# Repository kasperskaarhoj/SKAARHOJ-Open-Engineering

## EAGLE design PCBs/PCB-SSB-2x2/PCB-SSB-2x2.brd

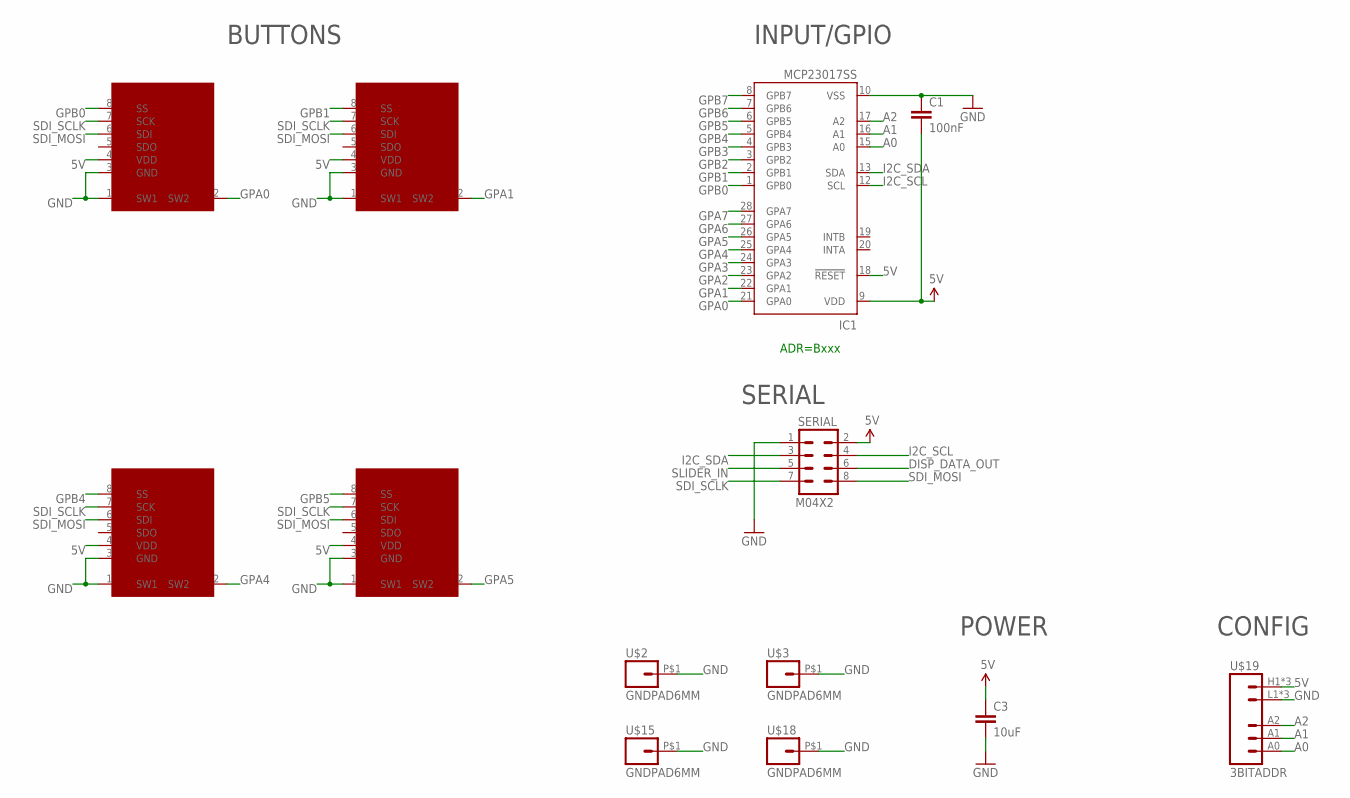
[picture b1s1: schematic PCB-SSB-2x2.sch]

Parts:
C1: 100nF; 0603-CAP
C3: 10uF; 0805
IC1: MCP23017SS; SSOP28; MPN MCP23017-E/SS
SERIAL: M04X2; 2X4
SSW1, SSW2, SSW5, SSW6: SMART_SWITCHSMART_SWITCH_8PIN; SMART_SWITCH
U$2, U$3, U$15, U$18: GNDPAD6MM; 3.2MMPAD6MM
U$19: 3BITADDR

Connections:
5V: C1.2, C3.1, IC1.9 (VDD), IC1.18 (!RESET), SERIAL.2, SSW1.4 (VDD), SSW2.4 (VDD), SSW5.4 (VDD), SSW6.4 (VDD), U$19.H1 (VCC), U$19.H2 (VCC), U$19.H3 (VCC)
A0: IC1.15 (A0), U$19.A0
A1: IC1.16 (A1), U$19.A1
A2: IC1.17 (A2), U$19.A2
DISP_DATA_OUT: SERIAL.6
GND: C1.1, C3.2, IC1.10 (VSS), SERIAL.1, SSW1.1 (SW1), SSW1.3 (GND), SSW2.1 (SW1), SSW2.3 (GND), SSW5.1 (SW1), SSW5.3 (GND), SSW6.1 (SW1), SSW6.3 (GND), U$2.P$1, U$3.P$1, U$15.P$1, U$18.P$1, U$19.L1 (GND), U$19.L2 (GND), U$19.L3 (GND)
GPA0: IC1.21 (GPA0), SSW1.2 (SW2)
GPA1: IC1.22 (GPA1), SSW2.2 (SW2)
GPA2: IC1.23 (GPA2)
GPA3: IC1.24 (GPA3)
GPA4: IC1.25 (GPA4), SSW5.2 (SW2)
GPA5: IC1.26 (GPA5), SSW6.2 (SW2)
GPA6: IC1.27 (GPA6)
GPA7: IC1.28 (GPA7)
GPB0: IC1.1 (GPB0), SSW1.8 (SS)
GPB1: IC1.2 (GPB1), SSW2.8 (SS)
GPB2: IC1.3 (GPB2)
GPB3: IC1.4 (GPB3)
GPB4: IC1.5 (GPB4), SSW5.8 (SS)
GPB5: IC1.6 (GPB5), SSW6.8 (SS)
GPB6: IC1.7 (GPB6)
GPB7: IC1.8 (GPB7)
I2C_SCL: IC1.12 (SCL), SERIAL.4
I2C_SDA: IC1.13 (SDA), SERIAL.3
SDI_MOSI: SERIAL.8, SSW1.6 (SDI), SSW2.6 (SDI), SSW5.6 (SDI), SSW6.6 (SDI)
SDI_SCLK: SERIAL.7, SSW1.7 (SCK), SSW2.7 (SCK), SSW5.7 (SCK), SSW6.7 (SCK)
SLIDER_IN: SERIAL.5

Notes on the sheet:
ADR=Bxxx
INPUT/GPIO
POWER
SERIAL
BUTTONS
CONFIG

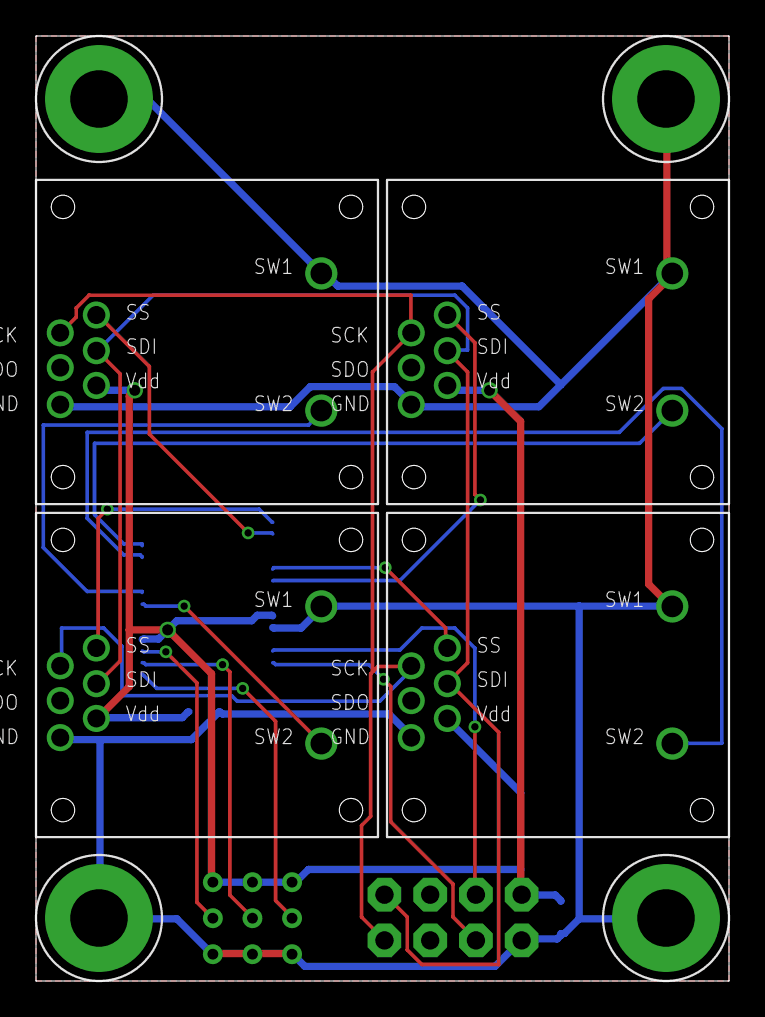
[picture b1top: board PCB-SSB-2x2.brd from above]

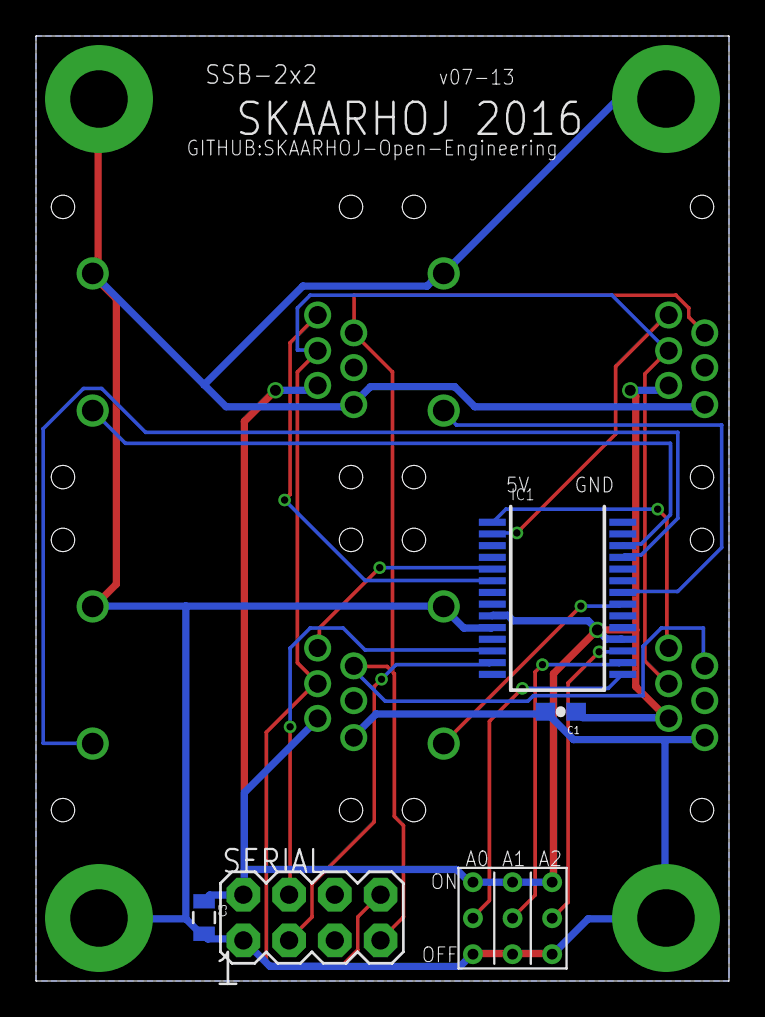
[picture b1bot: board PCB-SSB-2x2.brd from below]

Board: 2 copper layers, 38.5 x 52.5 mm, 13 parts (5 on the bottom side), 17 nets.

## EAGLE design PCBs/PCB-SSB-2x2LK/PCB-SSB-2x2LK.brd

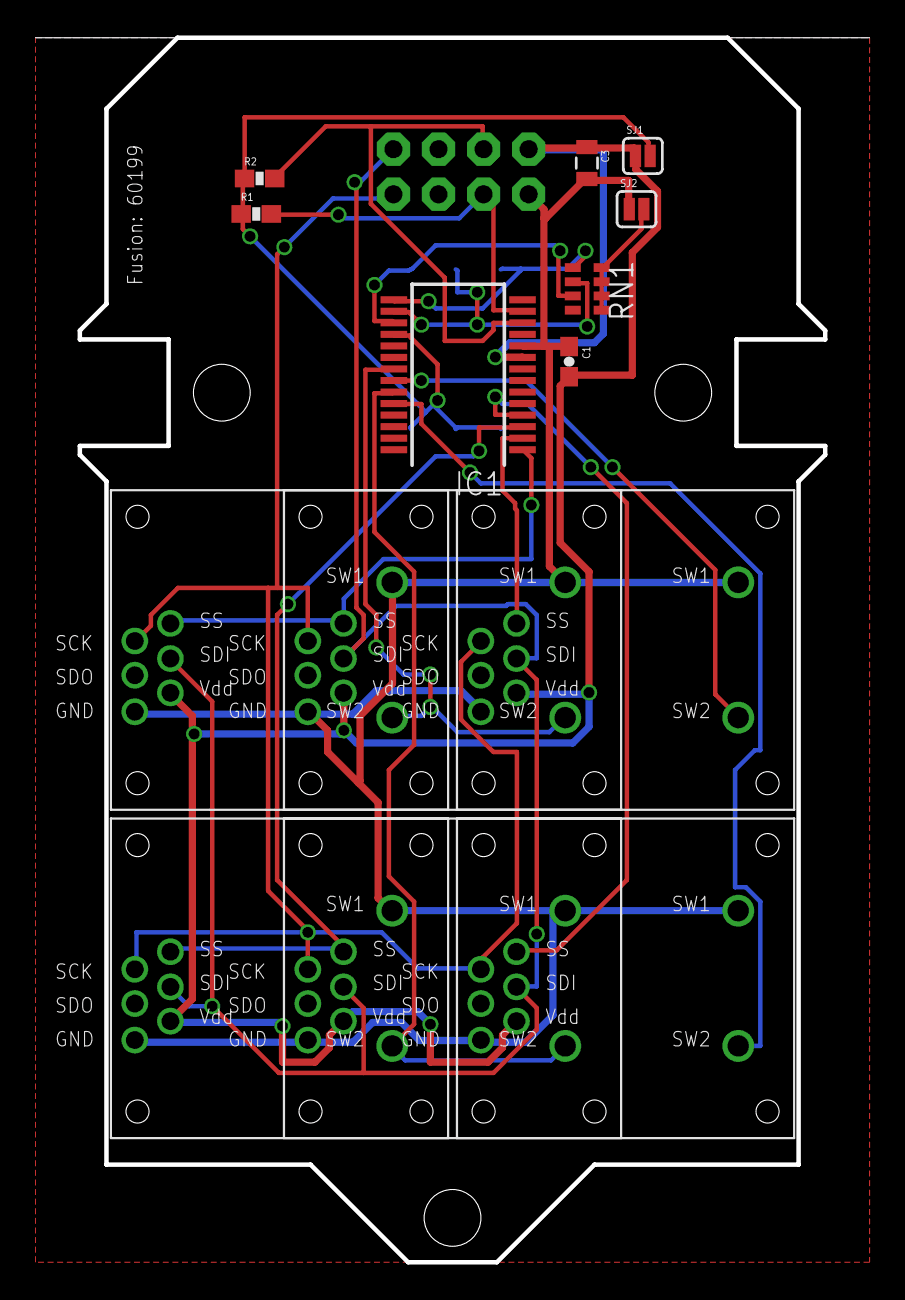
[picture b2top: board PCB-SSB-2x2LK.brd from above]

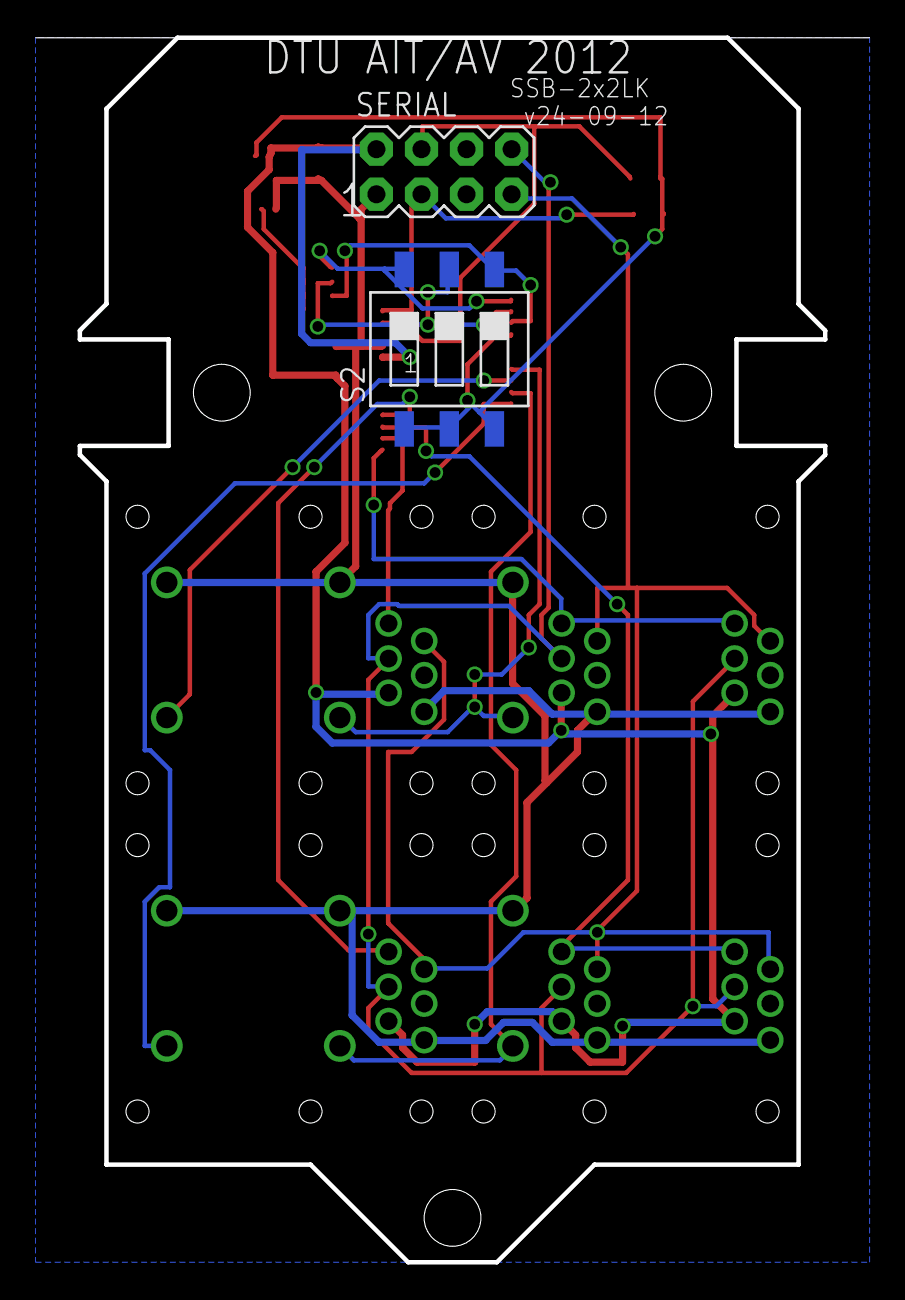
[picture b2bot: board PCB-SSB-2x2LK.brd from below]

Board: 2 copper layers, 42.0 x 69.0 mm, 16 parts (2 on the bottom side), 19 nets.

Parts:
C1: 100nF; 0603-CAP
C3: 10uF; 0805
IC1: MCP23017SS; SSOP28
R1, R2: 10K; 0603-RES
RN1: 10K; CAY16_HAND
S2: SWS003; SMS-003
SERIAL: M04X2; 2X4
SJ1, SJ2: SOLDERJUMPERNC; SJ_2S
U$2, U$3, U$4, U$5, U$6, U$7: SMART_SWITCHSMART_SWITCH_8PIN; SMART_SWITCH

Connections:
5V: C1.2, C3.1, IC1.9, SERIAL.2, SJ1.1, U$2.4, U$3.4, U$4.4, U$5.4, U$6.4, U$7.4
5VL: IC1.18, R1.1, R2.1, S2.1, S2.2, S2.3, SJ1.2
A0: IC1.15, RN1.5, S2.6
A1: IC1.16, RN1.6, S2.5
A2: IC1.17, RN1.7, S2.4
GND: C1.1, C3.2, IC1.10, SERIAL.1, SJ2.1, U$2.1, U$2.3, U$3.1, U$3.3, U$4.1, U$4.3, U$5.1, U$5.3, U$6.1, U$6.3, U$7.1, U$7.3
GNDL: RN1.1, RN1.2, RN1.3, RN1.4, SJ2.2
GPA0: IC1.21, U$2.2, U$6.2
GPA1: IC1.22, U$3.2
GPA2: IC1.23, U$4.2, U$7.2
GPA3: IC1.24, U$5.2
GPB0: IC1.1, U$2.8, U$6.8
GPB1: IC1.2, U$3.8
GPB2: IC1.3, U$4.8, U$7.8
GPB3: IC1.4, U$5.8
I2C_SCL: IC1.12, R2.2, SERIAL.4
I2C_SDA: IC1.13, R1.2, SERIAL.3
SDI_MOSI: SERIAL.8, U$2.6, U$3.6, U$4.6, U$5.6, U$6.6, U$7.6
SDI_SCLK: SERIAL.7, U$2.7, U$3.7, U$4.7, U$5.7, U$6.7, U$7.7

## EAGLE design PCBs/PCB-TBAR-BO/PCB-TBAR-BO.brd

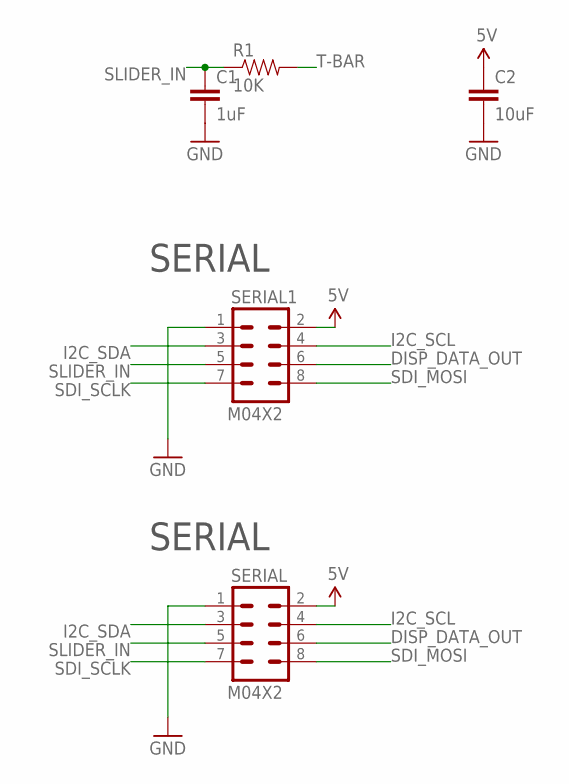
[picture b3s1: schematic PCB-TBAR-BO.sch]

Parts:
C1: 1uF; 0603-CAP
C2: 10uF; 0603-CAP
R1: 10K; 0603-RES
SERIAL, SERIAL1: M04X2; 2X4

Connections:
5V: C2.1, SERIAL.2, SERIAL1.2
DISP_DATA_OUT: SERIAL.6, SERIAL1.6
GND: C1.2, C2.2, SERIAL.1, SERIAL1.1
I2C_SCL: SERIAL.4, SERIAL1.4
I2C_SDA: SERIAL.3, SERIAL1.3
SDI_MOSI: SERIAL.8, SERIAL1.8
SDI_SCLK: SERIAL.7, SERIAL1.7
SLIDER_IN: C1.1, R1.1, SERIAL.5, SERIAL1.5
T-BAR: R1.2

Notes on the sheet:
SERIAL

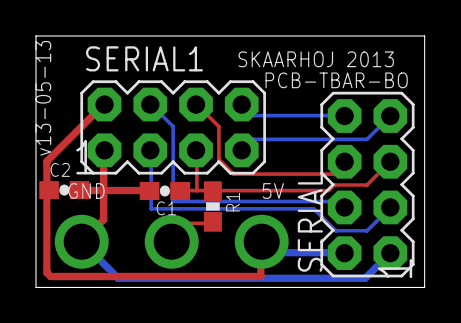
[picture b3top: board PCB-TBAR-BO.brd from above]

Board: 2 copper layers, 21.6 x 14.0 mm, 5 parts (0 on the bottom side), 8 nets.

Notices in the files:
parts and their libraries:
SparkFun: Licensing: CC v3.0 Share-Alike You are welcome to use this library for commercial purposes.
